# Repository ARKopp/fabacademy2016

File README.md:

#Fablab Academy 2016 - How to make anything

[BACK to START](start)

[FINAL PROJECT](final) / [WEEK 1](week1) / [COMPUTER AIDED DESIGN](week2) / [COMPUTER-CONTROLLED-CUTTING](week3) / [ELECTRONICS PRODUCTION](week4) / [3D SCANNING & PRINTING](week5) / [ELECTRONICS DESIGN 1](week6)  / [COMPUTER-CONTROLLED MACHINING](week7) / [EMBEDDED PROGRAMING ](week8) / [MECHANICAL AND MACHINE DESIGN](week9) / [INPUT DEVICES](week10) / [3D MOULDING AND CASTING ](week11) / [OUTPUT DEVICES](week12) /  [COMPOSITES](week13) / [EMBEDDED NETWORKING & COMMUNICATIONS](week14) / [INTERFACE AND APPLICATION PROGRAMMING ](week15) / [APPLICATIONS AND IMPLICATIONS ](week16) / [INVENTION, INTELLECTUAL PROPERTY, AND BUSINESS MODELS](week17) / [PROJECT DEVELOPMENT ](week18) /  

This year (2016) I will participate in the Fabacademy course called "How to make anything" with about 350 other students in over 80 Fablabs all over the world. I will participate at the Fablab Barcelona. On this website I will document my course acitivty and my [final project](final). The student websites of the bast years you find [here](http://archive.fabacademy.org/).

# About

Hi, I am Andreas a 32 year old guy from Munich Germany who makes a living tinkering and teaching kids coding and eletronics. Also I am building up my own fablab and raspberry pi academy at the moment focused on small and big kids called [erfindergarden](http://www.erfindergarden.de) and plan a fablab world tour after the academy program with my [Mincraft Hacking workshop](https://raspi-grundlagen-wien.eventbrite.de).

## My Story

I studied business and engineering and first started working in software sales. But I realized that beeing an employee is nothing for me so started working for myself in 2011.

My creazy journey started when I filmened and help creating a post-it art work of Steve Jobs at the Apple store after his death. This youtube video went viral and since then I have been creating [post-it art portraits](http://www.postitartreators.com) and pictures for conferences, commercials and art shows. 

In 2013 I build the [pixomat](http://www.pixomat.co) a pixel photobooth in a shopwindow on the other site of the street of the Steve Jobs portrait and since then got deeper and deeper into the maker world learning coding, electronics, raspberry pi, 3D Printing, Laser Cutting and since 2014 started teaching that knowledge to kids and also started freelancing for [hybris/SAP labs](http://labs.hybris.com) as a creative technologist.

## So why do I do the fabacademy ?

I want to gain deeper knowledge in the fablab technolgies and get to know other maker and share knowledge and experiences with them  I also think it is a good way to focus my energy on a project I have been dreaming to build for a while - [the stickomat](final).

## License

After filling out [these questions](https://creativecommons.org/choose/) on the creative commons website I decided to license this website and my work for fabacademy under a Creative Commons Attribution 4.0 International License.

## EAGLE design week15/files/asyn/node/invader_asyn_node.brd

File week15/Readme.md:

[BACK to START](../)

[FINAL PROJECT](../final) / [WEEK 1](../week1) / [COMPUTER AIDED DESIGN](../week2) / [COMPUTER-CONTROLLED-CUTTING](../week3) / [ELECTRONICS PRODUCTION](../week4) / [3D SCANNING & PRINTING](../week5) / [ELECTRONICS DESIGN](../week6)  / [COMPUTER-CONTROLLED MACHINING](../week7) / [EMBEDDED PROGRAMING ](../week8) / [MECHANICAL DESIGN](../week9) / [MACHINE DESIGN](../week10) / [INPUT DEVICES](../week11) / [3D MOULDING AND CASTING](../week12) / [OUTPUT DEVICES](../week13) / [COMPOSITES](../week14) / [EMBEDDED NETWORKING & COMMUNICATIONS](../week15) / [INTERFACE AND APPLICATION PROGRAMMING ](../week16) / [APPLICATIONS AND IMPLICATIONS ](../week17) / [INVENTION, INTELLECTUAL PROPERTY, AND BUSINESS MODELS](../week18) / [PROJECT DEVELOPMENT ](../week19)  

# Week 15 - Networking & Communications (WIP)

May 11 - May 18

[Lecture](http://academy.cba.mit.edu/classes/networking_communications/index.html), [Video](http://archive.fabacademy.org/archives/2016/master/videos/05-11/index.html)

~~~
*Weeks Assignment*

design and build a wired &/or wireless 
network connecting at least two processors

~~~

I can decided to make all the boards and started with the two Serial Boards. One is the node and one the bridge. 

## Invader Serial asynchronous

### Making Cabels 

First I put together 3 serial cables like for the FabISP as well. Then i started designing. 

### Node

* [x] Attiny 45
* [x] 2x3 Connector
* [x] 2x2 Connector
* [x] 1k Resistor
* [x] LED
* [x] 10K Resistor
* [x] 1uF Cap

This time no new components to look at. I just repositioned the LEDs to get an Invader eye. 

### Bridge

* [x] Attiny 45
* [x] 2x3 Connector
* [x] 2x2 Connector
* [x] 1K Resistor
* [x] LED
* [x] 10K Resistor
* [x] 1uF Cap
* [x] FTDI Connector

Because I wanted to position the FTDI connectors on the feet of the invader I had do add 6 0 Ohm. If you can figure out how to avoid that let me know. You can find the schematic and the brd file in the project files download link below.

### Milling and Stuffing 

Here my boards are in my other mill. I really got better in working with my mill after making all output devices. As I broke a bit because after pulling out one Invader the PCB was not sticking to the plate so good anymore I first finish milling all 4 invaders and the pull out all 4 at the same time or will use a smaller board when I only want to mill one little thing. 

## Programming 

The node I could program without problem. What you have to do is to assign the   bridge a 0 and the nodes a 1, 2, 2 etc.

## Invader Serial I2C

During the last years I worked with Arduino and Pis I always heared these three letters but never quite understood. 

So this time I first read a couple of articles about I-squared-C to understand it better. It was invented in 1982 to use as communication betweend Integrated Curcuits in CD Players and TVs. In Atmel I2X is called TWI (Two-Wire-Interface in their chops which is technically the same.

I2C needs two data lines. One seriell Clock line (SCL) and one for Data (SDA) and is used for communication for short distances. The speed is 100kbit/s standard and 10kbit/s low-speed mode. 

### Node

* [x] Attiny 45
* [x] 2x3 Connector
* [x] 2x2 Connector
* [x] 1k Resistor
* [x] LED
* [x] 3 x 10K Resistor
* [x] 1uF Cap

### Bridge

* [x] Attiny 45
* [x] 2x3 Connector
* [x] 2x2 Connector
* [x] 3x  10K Resistor
* [x] 1uF Cap
* [x] FTDI Connector

### Programming

When programming the node and the bridge with the c code you your are using the same code only that the bridge gets a `0` and the node gets a `1` you can then add more node with '2', '3' etc. 

###SPI (Serial Peripheral Interface)

Also when working with Arduino and Pi hats I have came across theses three letters SPI. Here a great [introduction](https://www.arduino.cc/en/Reference/SPI) of SPI on the Arduino homepage. 

For example I have the explorer hat from Pimorino. There the Raspberry pi would be the master and the the chip on the explorer hat would be the slave.

These are the lines used:

* MISO (Master In Slave Out) - The Slave line for sending data to the master,
* MOSI (Master Out Slave In) - The Master line for sending data to the peripherals,
* SCK (Serial Clock) - The clock pulses which synchronize data transmission generated by the master

and one line specific for every device:
* SS (Slave Select) - the pin on each device that the master can use to enable and disable specific devices.

### Invader Bluetooth

Coming up.

### Invader ESP

Coming up. 

## Project Files

[Download](https://drive.google.com/folderview?id=0B3iYmii-HJ7TOWdGSWFwd1ZlZG8&usp=sharing) all project files from this assignment from my Google Drive.

## Learnings

* get faster in designing in Eagle
* master my Othermill machine

## Feedback

[Twitter](http://www.twitter.com/andreaskopp) me or email me at [andreasrkopp at gmail dot com](mailto:andreasrkopp@gmail.com).

Or chat with me on gitter.

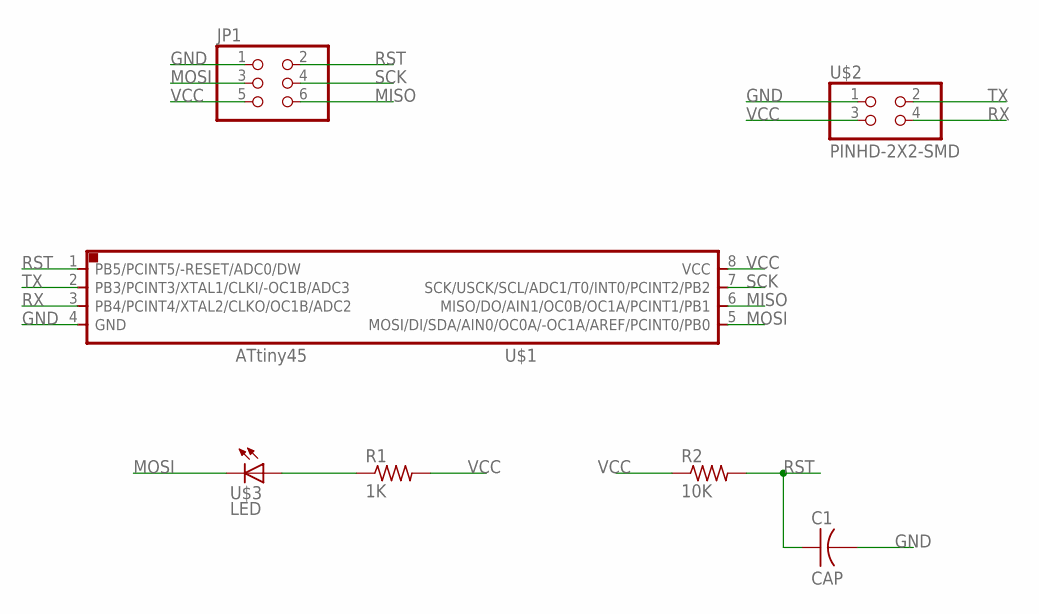
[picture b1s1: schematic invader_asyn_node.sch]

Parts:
C1: CAP; C1206FAB
JP1: PINHD-2X3-SMD; 2X03SMD
R1: 1K; R1206
R2: 10K; R1206
U$1: ATTINY45SI; SOIC8
U$2: PINHD-2X2-SMD; 2X02SMD
U$3: LED; LED1206FAB

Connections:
GND: C1.2, JP1.1, U$1.4 (GND), U$2.1
MISO: JP1.6, U$1.6 (MISO/DO/AIN1/OC0B/OC1A/PCINT1/PB1)
MOSI: JP1.3, U$1.5 (MOSI/DI/SDA/AIN0/OC0A/-OC1A/AREF/PCINT0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), U$3.2 (C)
unnamed: R1.1, U$3.1 (A)
RST: C1.1, JP1.2, R2.2, U$1.1 (PB5/PCINT5/-RESET/ADC0/DW)
RX: U$1.3 (PB4/PCINT4/XTAL2/CLKO/OC1B/ADC2), U$2.4
SCK: JP1.4, U$1.7 (SCK/USCK/SCL/ADC1/T0/INT0/PCINT2/PB2)
TX: U$1.2 (PB3/PCINT3/XTAL1/CLKI/-OC1B/ADC3), U$2.2
VCC: JP1.5, R1.2, R2.1, U$1.8 (VCC), U$2.3

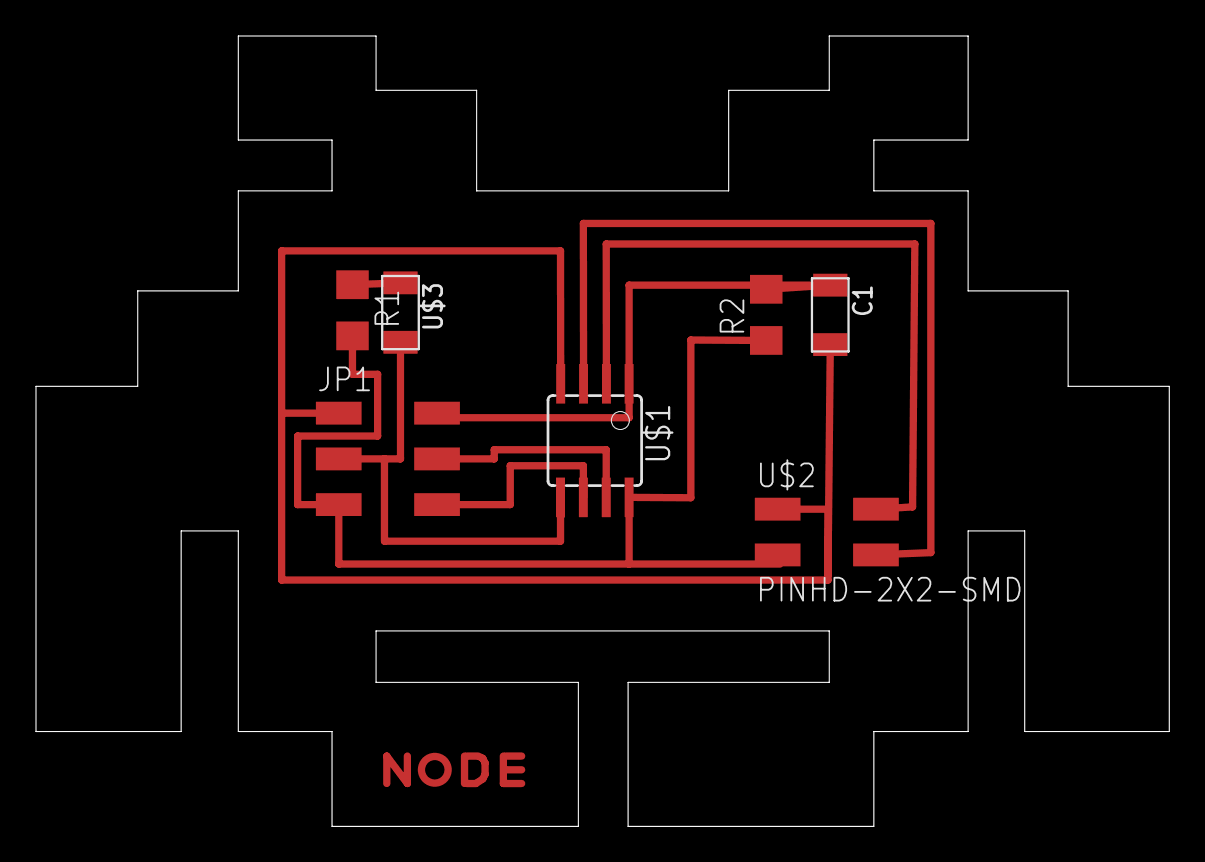
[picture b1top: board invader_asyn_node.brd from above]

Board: 2 copper layers, 63.0 x 43.9 mm, 7 parts (0 on the bottom side), 9 nets.

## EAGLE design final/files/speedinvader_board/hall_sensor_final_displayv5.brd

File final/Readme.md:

[BACK to START](../)

[FINAL PROJECT](../final) / [WEEK 1](../week1) / [COMPUTER AIDED DESIGN](../week2) / [COMPUTER-CONTROLLED-CUTTING](../week3) / [ELECTRONICS PRODUCTION](../week4) / [3D SCANNING & PRINTING](../week5) / [ELECTRONICS DESIGN](../week6)  / [COMPUTER-CONTROLLED MACHINING](../week7) / [EMBEDDED PROGRAMMING ](../week8) / [MECHANICAL DESIGN](../week9) / [MACHINE DESIGN](../week10) / [INPUT DEVICES](../week11) / [3D MOLDING AND CASTING](../week12) / [OUTPUT DEVICES](../week13) /  [COMPOSITES](../week14) / [EMBEDDED NETWORKING & COMMUNICATIONS](../week15) / [INTERFACE AND APPLICATION PROGRAMMING ](../week16) / [APPLICATIONS AND IMPLICATIONS ](../week17) / [INVENTION, INTELLECTUAL PROPERTY, AND BUSINESS MODELS](../week18) / [PROJECT DEVELOPMENT ](../week19)  

--------------------------------------------------------------------

***[Initial Idea  - the stickomat](./ideas)***

***[The Speedinvader](./)***

***[Process - How did I make it?](./process)***   

--------------------------------------------------------------------

## What did I make?

I made a bamboo composite skateboard and a skateboard speedometer that measures the speed with a magnetic sensor on the wheel of the board and displays it on a tiny oled display on top. 

But I learned to so much more in the last 6 months and most importantly I won friends from all over the world. Thank you all for the great time, your help and your couches. Also special thanks to my instructors Ferdi and Santi for your support. I could not have made it with you!

The Barcelona Fabacademy Class of 2016

## Final project video and Presentation

* [my final project Video live from the Chino infront of the Fablab Barcelona](../presentation.mp4)
* [presenting it to Neil Gerschenfield ](http://archive.fabacademy.org/archives/2016/master/videos/06-22/index.html)

## Composite Skateboard in week 14

I made the bamboo composite skateboard in [week14](../week14). 

## Bill of Materials (Version 7. Juli 2016)

* bamboo sheets 4 mm
* penny board wheels and beerings
* penny board axle
* black filament 
* one blank circuit board
* hall sensor
* tiny oled display
* Attiny85
* 4x 10k Resistor
* 1uF Capacitor
* 2 X SMD LEDs
* Battery Holder
* little neodyne magnet
* 2 Screws 

* [adafruit voltage booster](https://www.adafruit.com/products/2465)
* Lipo Battery 3,7 V

### What are my future plans for the project?

This is just a first version of the speedinvader. I could not complete all things I wanted to do but I want to keep on working.

* <del>Design and mill Hall Breakout v1</del>
* <del>Program Board v1<del>
* <del>Code for OLED Display in Arduino</del>
* <del>Add voice and Button v3</del>
* <del>Mill and solder board v3</del>
* <del>Design and mill Hall Breakout Double Sided</del>
* <del>Design Housing</del>
* <del>3D Print Housing</del>
* <del>make slide</del> 
* <del>make video</del>
* make a smaller board version
* make the breakoutboard fit better
* Design Waterproof Housing
* Mold Housing
* send board to be made in China
* make a bike version
* develop a workshop
* experiment with hex images

* optional: Raspberry Pi Zero HAT
* optional: add Bluetooth and Radio
* optional: Make a Light blue bean hat

##  Continue while Repositry locked

While the repository is locked I will continue to work on the speedinvader on my own git hub [here](github [here](https://github.com/ARKopp/fabacademy2016). 

## All files you need to rebuild it

It is still not perfect, so when you want to replicate this you may wont to wait a bit until I have made the next version. 

### Electronics

[hall_sensor_final_displayv5.brd](./files/speedinvader_board/hall_sensor_final_displayv5.brd)

[hall_sensor_final_displayv5.sch](./files/speedinvader_board/hall_sensor_final_displayv5.sch)

[hall_sensor_break_out.brd](./files/breakout_board/hall_sensor_break_out.brd)

[hall_sensor_break_out.sch](./files/breakout_board/hall_sensor_break_out.sch)

### Code

[firmwarespeedinvader.ino (you need all libraries)](./files/firmware_speedinvader/firmware_speedinvader)

### Skateboard

[skateboard design (rhino)](../week14/files/skateboard_file.3dm)

### Case

[CaseBottom, Case Top, Skateboard Holder (Tinkercad)](https://tinkercad.com/things/1azkU2S8nCk)

[CaseTop](./files/design_files/case_top.stl)

[CaseBottom](./files/design_files/scase_bottom.stl)

[Skateboard Mount](./files/design_files/skateboard_mount.stl)

I will make speedinvader PCB much smaller because I do not think that is very practical.

## Feedback ?

[Twitter](http://www.twitter.com/andreaskopp) me or [email me at andreasrkopp at gmail dot com](mailto:andreasrkopp@gmail.com) I am very happy to help. 

Or chat with me on gitter.

## License

In [week18 ](../week18) I chose the license for the speedinvader. 

The project is licensed under Attribution-ShareAlike 4.0 International (CC BY-SA 4.0). So if you are creating a derivative of my speedometer you should license it as well under CC BY-SA 4.0 license and credit me like above. This is the same license Arduino is using for their hardware.

[BACK to TOP](../final)

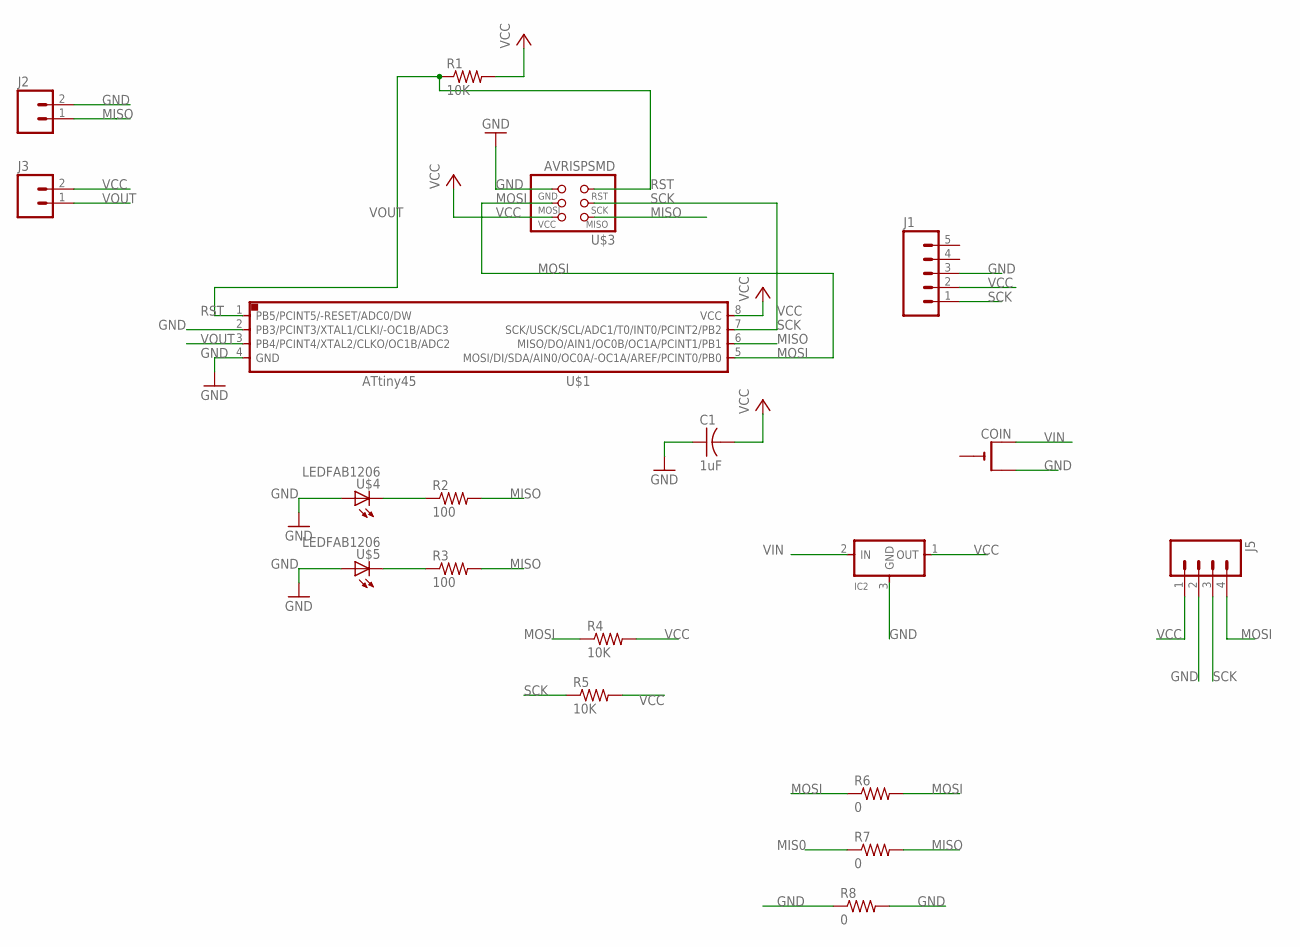
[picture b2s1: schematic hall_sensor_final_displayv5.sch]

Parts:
C1: 1uF; C1206FAB
COIN: CR2032THM; CR2032-THRU
IC2: REGULATORSOT23; SOT23
J1: M05LOCK; 1X05_LOCK
J2, J3: M02POLAR_LOCK; MOLEX-1X2_LOCK
J5: M04LOCK; 1X04_LOCK
R1, R4, R5: 10K; R1206FAB
R2, R3: 100; R1206FAB
R6, R7, R8: 0; R1206FAB
U$1: ATTINY45SI; SOIC8
U$3: AVRISPSMD; 2X03SMD
U$4, U$5: LEDFAB1206; LED1206FAB

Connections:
GND: C1.1, COIN.+2 (+1), IC2.3 (GND), J1.3, J2.2, J5.2, R8.1, R8.2, U$1.2 (PB3/PCINT3/XTAL1/CLKI/-OC1B/ADC3), U$1.4 (GND), U$3.6 (GND), U$4.1 (A), U$5.1 (A)
MIS0: R7.1
MISO: J2.1, R2.2, R3.2, R7.2, U$1.6 (MISO/DO/AIN1/OC0B/OC1A/PCINT1/PB1), U$3.1 (MISO)
MOSI: J5.4, R4.1, R6.1, R6.2, U$1.5 (MOSI/DI/SDA/AIN0/OC0A/-OC1A/AREF/PCINT0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), U$3.4 (MOSI)
unnamed: R2.1, U$4.2 (C)
unnamed: R3.1, U$5.2 (C)
RST: R1.1, U$1.1 (PB5/PCINT5/-RESET/ADC0/DW), U$3.5 (RST)
SCK: J1.1, J5.3, R5.1, U$1.7 (SCK/USCK/SCL/ADC1/T0/INT0/PCINT2/PB2), U$3.3 (SCK)
VCC: C1.2, IC2.1 (OUT), J1.2, J3.2, J5.1, R1.2, R4.2, R5.2, U$1.8 (VCC), U$3.2 (VCC)
VIN: COIN.+1 (+), IC2.2 (IN)
VOUT: J3.1, U$1.3 (PB4/PCINT4/XTAL2/CLKO/OC1B/ADC2)

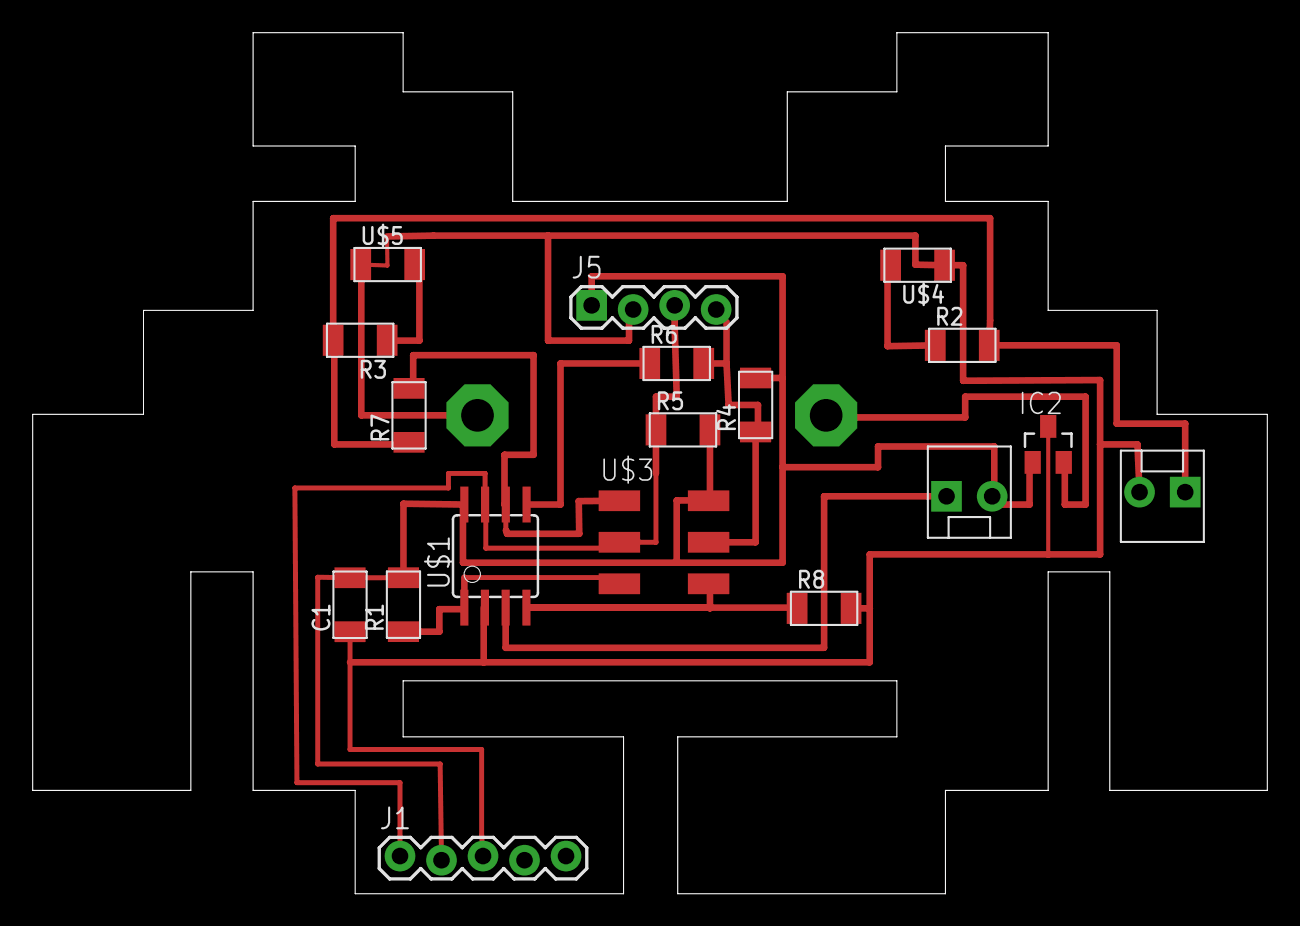
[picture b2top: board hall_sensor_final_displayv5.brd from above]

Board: 2 copper layers, 75.6 x 52.7 mm, 19 parts (1 on the bottom side), 10 nets.

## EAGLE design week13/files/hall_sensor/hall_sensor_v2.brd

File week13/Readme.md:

[BACK to START](../)

[FINAL PROJECT](../final) / [WEEK 1](../week1) / [COMPUTER AIDED DESIGN](../week2) / [COMPUTER-CONTROLLED-CUTTING](../week3) / [ELECTRONICS PRODUCTION](../week4) / [3D SCANNING & PRINTING](../week5) / [ELECTRONICS DESIGN](../week6)  / [COMPUTER-CONTROLLED MACHINING](../week7) / [EMBEDDED PROGRAMING ](../week8) / [MECHANICAL DESIGN](../week9) / [MACHINE DESIGN](../week10) / [INPUT DEVICES](../week11) / [3D MOLDING AND CASTING](../week12) / [OUTPUT DEVICES](../week13) / [COMPOSITES](../week14) / [EMBEDDED NETWORKING & COMMUNICATIONS](../week15) / [INTERFACE AND APPLICATION PROGRAMMING ](../week16) / [APPLICATIONS AND IMPLICATIONS ](../week17) / [INVENTION, INTELLECTUAL PROPERTY, AND BUSINESS MODELS](../week18) / [PROJECT DEVELOPMENT ](../week19)

# Week 13 - OUTPUT DEVICES

May 10

[Lecture](http://academy.cba.mit.edu/classes/output_devices/index.html), [Video](http://archive.fabacademy.org/archives/2016/master/videos/04-20/index.html)

~~~
*Weeks Assignment*

* add an output device to a micro controller board you've designed 
* program it to do something

~~~

For this assignment I decided to get the LEDs of my space invader to work and make a second version with two RGB LEDs. In the end I did all output devices and made a little invader army.

## Change the code to turn on the LEDs

For [Input Devices](../week11) I had made a space invader but failed to get the LEDs to turn on. 

I first checked if I had soldered them correctly with the Green Line to the Ground. And I had. I also checked the Resistor Value again. I used the red LED and after looking into the [Fabacademy Inventory](https://docs.google.com/spreadsheets/d/1U-jcBWOJEjBT5A0N84IUubtcHKMEMtndQPLCkZCkVsU/pub?single=true&gid=0&output=html) I found the Red Led had the number 160-1167-2-ND. Looking that up on the digikey website I found the Forward Voltage is 1.8 V and the forwward current is 40 mA which result in a Resistor of 82 Ohms and I am using 499 Ohms at the moment so I will change the resistor to 100 Ohms. 

***Update 8. Mai 2016:***

I changed the Resistors from 499 Ohm to 100 Ohms and finally got the invader eyes to light up! But the LEDs I connected to and MOSI and MISO which turned out to be Pin 0 and Pin 1 in then Arduino IDE.

***Update 14. Mai 2016:***

Next I wanted to get finally get my hall effect Sensor working. The sensor has 3 legs, VCC, GND and VOUT which I connected to PB4. 

Because I still did not learn enough C I looked for some Arduino Code. 

But I found [some code](http://playground.arduino.cc/Code/HallEffect) on the Arduino Website and some other code [here](http://www.hobbytronics.co.uk/arduino-tutorial11-hall-effect) and [here](http://www.instructables.com/id/DIY-bike-tachometer/step3/Upload-code/).

Still I was not able to get any reading. 

I check with the python file from Neil and with a different cable but still no reading. So I think I destroyed my sensor somehow. I will check the sensor on an Arduino to see if its really the sensor. 

***Update 22. Mai 2016:***

I finally found the time to revise my space invader board and added a through hole connector, I think the chance that they break off is much lower then the ISP Connectors that only have a connection with the top of the board. You can find the design in the project download in input devices. I think I found this connector in the sparkfun library (Eagle: 1x5 Lock).

http://www.instructables.com/id/Hall-effect-sensor/step2/Range-of-a-Hall-effect-Sensor/

http://www.instructables.com/id/Arduino-Skateboard-Speedometer/step3/The-Arduino-Code/

http://www.instructables.com/id/DIY-SPEEDOMETER-AND-ODOMETER/step3/THE-CODE/

## Invader RGB

Next I wanted to turn my invader into an RGB Invader. Also I wanted to avoid doing the fabmodules step and the step to turn create the black and white images. I first Vectorized my space invader image with Inkscape and exported as dxf and imported into Eagle in the Dimension Layer with File>Import>DXF.

I started with Neils Design and added another LED and resistor.  

### Bill of Material

* [x] 1 x RGB Led
* [x] 2 x 1k Resistor 
* [x] 1 x 499 ohm
* [x] 1x 1Ok Resistor
* [x] 1 x 1uF Capacitor
* [x] 1x Attiny 45
* [x] 1x 2X3 AVR ISP Connector
* [x] 1x 2X2 AVR ISP Connector (Eagle:PINHD-2x2-SMD) <--- look exactly with this name when your searching
* [x] 1x LM3480IM3-5.0 Voltage Regulator (Eagle: RegulatorSot23)
* [x] 1x 100 Ohm Resistor
* [x] 1x Red LED

### Schematic and Board Design

First I looked at the Datasheet of the RGB LED to find how I need to connect it. 

I connected it like this. 

Then I added all the parts to the board. I had some problems to find the Voltage Regulator and the 2x2 Connector but managed in the end. 

It was the first time I used the 5V Voltage Regulator 100MA (LM3480IM3-5.0/NOPBCT-ND) so I looked it on Digikey and found out the you can put in as much as 30V and it always puts out 5V.

***Update 17. Mai 2016***

After doing all the output board I realized that their are two different 5V voltage regulators in the Inventory one small one with a small 100mA footprint (LM3480IM3-3.3/NOPBCT-ND)  ... 

and a 1A one (LM3480IM3-5.0/NOPBCT-ND) with a big foot print. 

All the boards are usign the small one only the SERVO board is using the big one. 

For my RGB Board with the extra LED I did not manange to connect the RGB and the LED with out adding a O Ohm Resistor and two jumpers. 

In the end I did a new board just with one RGB LED. 

```
sudo make -f hello.speaker.45.make program-avrisp2

```

### Milling

I saved the Brd file and milled with my Othermill.  

### Stuffing and Programming 

Then I stuffed the board and tried to program it but got an error. Only after checking all connections and using another ISP I found that I had positioned the RGB LED wrongly. The little white corner is not the Power put R for Red. In my case it is on the right top side. 

For Programming you download the [Make](http://academy.cba.mit.edu/classes/output_devices/LCD/hello.LCD.44.make) and the [C](http://academy.cba.mit.edu/classes/output_devices/LCD/hello.LCD.44.c) file into a folder and open them in Terminal. Because I stepped on my FabISP and damaged the connector I used the AVRisp I bought. I also find it quite difficult to remember the GND and VCC Side of the Cable of my FabISP.  

I would love to do some screen printing soon to print lables on the boards before I mill them. 

```
sudo make -f hello.RGB.45.make program-avrisp2

```
And it was successful! Because I could not get my board to work but the second board without the extra LED worked.

The first board I also tried to fix but damaged the Pads of the LED when desoldering and could not fix it again.

### Invader LCD Screen

* [x] Attiny44
* [x] 20 MHz Resonator
* [x] 10 K Resistor
* [x] 2x3 ISP Connector
* [x] 1 uF Cap
* [x] 5V Voltage Regulator
* [x] 100 K Resistor
* [x] 1K Resistor
* [x] 5x2 Connector
* [x] 2x3 Connector

### Invader Speaker

* [x] speaker
* [x] Attiny45
* [x] 10k Resistor
* [x] Voltage Regulator 5V
* [x] 2X 2x2 Connector
* [x] 1X 2x3 Connector

Only after I did not get a green light with my AVR I realized that I forgot a connection in my schematic bitween the VCC and the 10K Resistor. After fixing that with a little wire I finally got the greenlight and programmed it. 

```
sudo make -f hello.speaker.45.make program-avrisp2
```

Thank you!

### Invader Servo

* [x] Attiny44
* [x] 10 K Resistor
* [x] 20 Mhz Resonator
* [x] 22 uF Capacitor
* [x] 5 V Voltage Regulator Big 1A (Eagle: 
* [x] 2x 3x2 ISP Connectors
* [x] 2x2 ISP Connectors
* [x] 0 Ohm 

### Invader Brush DC

To control the DC Motor we need a [H-Bridge](http://www.digikey.com/product-detail/en/A4953ELJTR-T/620-1428-1-ND/2765622). A DC Motor can only run at one speed and  forward or backwards. So I am using a A4952 from Allegro to turn the Motor on and off really fast to control the speed this way. 

* [x] Attiny44
* [x] 10K Resistor
* [x] 10uF Cap
* [x] 2x 1uF Cap
* [x] A 4953 H-Bridge
* [x] 5 V Voltage Regulator
* [x] 2x  2x2 ISP Conncetors

First I forget to connect some line but I realized it before soldering. Here I realize I have to be more careful and check all lines and if I have added all components. So I milled again and finished the board. 

Always I have to cut the line for the voltage generator with a knife. So I wander how can I avoid this?

### Invader Stepper Uni

* [x] Attiny44
* [x] 3 x 1uF Capacitator 
* [x] 2 x 10uF Capacitator (I forgot this at first!)
* [x] 10 K
* [x] 5 V Regulator
* [x] 2 X 2x3 Connectors
* [x] 2x2 Connector
* [x] 4 x N Mosef

### Invader LED Array (coming soon)

This one I would like to do on a two sided PCB. So I have the microcontroller on the back and all the led on the front of the Invader. 

* 20 X O hm 
* 5 x 499 Ohm
* 1 uF
* 10 K Resistor
* 2x3 ISP Connector
* 2x2 ISP Connector
* Voltage Regulator 5V

### Invader Video (Coming soon)

Coming soon. 

* [x] Attiny44
* [x] 20 MHz Resonator
* [x] 10 K Resistor
* [x] 1 K Resistor
* [x] 1 uF Cap
* [x] 499 Resistor
* [x] 2x2 Connector
* [x] 5x2 Connector

## Project Files

[Download](https://drive.google.com/folderview?id=0B3iYmii-HJ7TdHh1VUJGRzdHalE&usp=sharing) all project files I ued for this assignment from my Google Drive. I have uploaded the improved invader_hall and the invader_rgb also to the repository. Also I made an invader with a coin cell battery that I linked here. 

[invader-rgb_working.brd](.files/invader_rgb/invader-rgb_working.brd)

[invader-rgb_working.sch (save as)](.files/invader_rgb/invader-rgb_working.sch)

[hall_sensor_v2.sch](.files/hall_sensor/hall_sensor_v2.sch)

[invader_vector_final.dxf (file I imported on Dimension 20 Layer)](./files/invader_vector_final.dxf)

[invader_coin2.brd](.files/invader_coin/invader_coin2.brd)   

[invader_coin2.sch (save as) ](.files/invader_coin/invader_coin2.sch)

## Learnings

* get faster in designing in Eagle
* master my Othermill machine
* understand all electronic components used better
* trouble shoot a board (first check all connections from connector to chip, shorts on connector, then if chip gets 5V)

## Feedback

[Twitter](http://www.twitter.com/andreaskopp) me or [email me at andreasrkopp at gmail dot com](mailto:andreasrkopp@gmail.com).

Or chat with me on gitter.

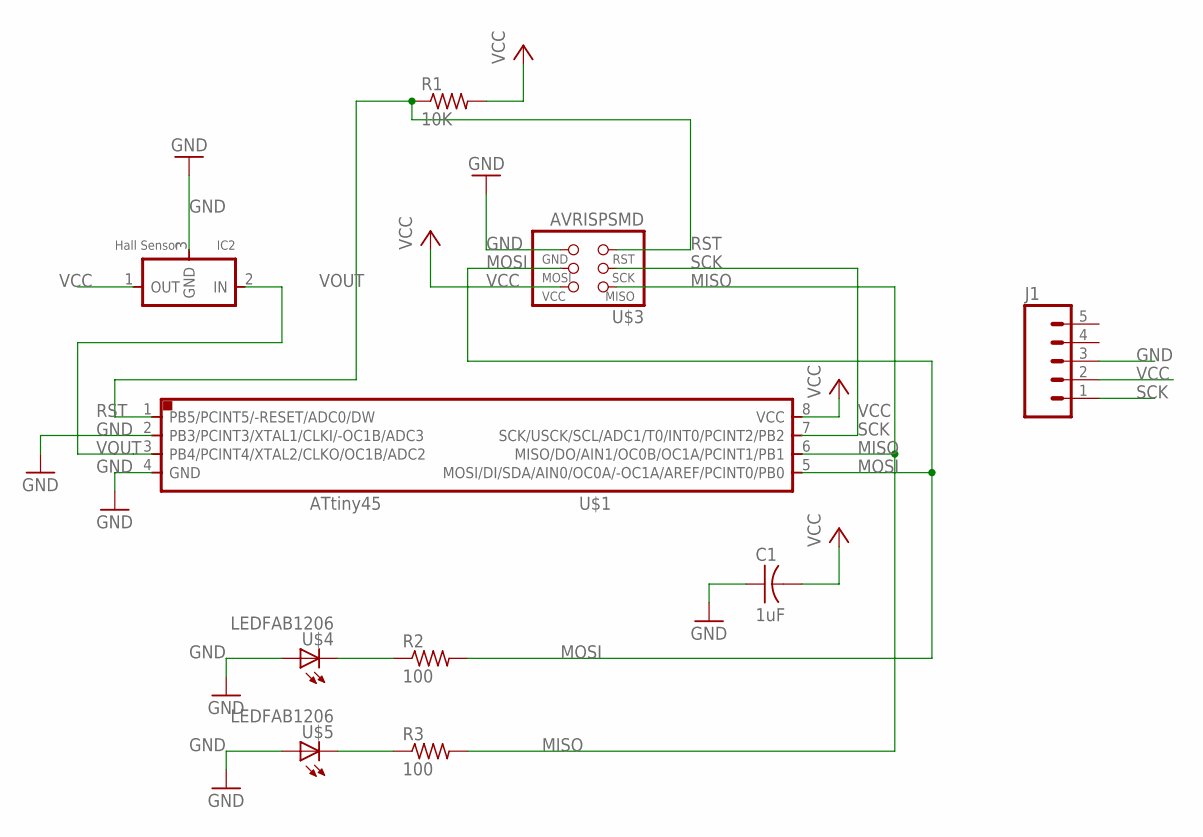
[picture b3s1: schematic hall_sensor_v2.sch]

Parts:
C1: 1uF; C1206FAB
IC2: Hall Sensor; SOT23
J1: M05LOCK; 1X05_LOCK
R1: 10K; R1206FAB
R2, R3: 100; R1206FAB
U$1: ATTINY45SI; SOIC8
U$3: AVRISPSMD; 2X03SMD
U$4, U$5: LEDFAB1206; LED1206FAB

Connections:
GND: C1.1, IC2.3 (GND), J1.3, U$1.2 (PB3/PCINT3/XTAL1/CLKI/-OC1B/ADC3), U$1.4 (GND), U$3.6 (GND), U$4.1 (A), U$5.1 (A)
MISO: R3.2, U$1.6 (MISO/DO/AIN1/OC0B/OC1A/PCINT1/PB1), U$3.1 (MISO)
MOSI: R2.2, U$1.5 (MOSI/DI/SDA/AIN0/OC0A/-OC1A/AREF/PCINT0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), U$3.4 (MOSI)
unnamed: R2.1, U$4.2 (C)
unnamed: R3.1, U$5.2 (C)
RST: R1.1, U$1.1 (PB5/PCINT5/-RESET/ADC0/DW), U$3.5 (RST)
SCK: J1.1, U$1.7 (SCK/USCK/SCL/ADC1/T0/INT0/PCINT2/PB2), U$3.3 (SCK)
VCC: C1.2, IC2.1 (OUT), J1.2, R1.2, U$1.8 (VCC), U$3.2 (VCC)
VOUT: IC2.2 (IN), U$1.3 (PB4/PCINT4/XTAL2/CLKO/OC1B/ADC2)

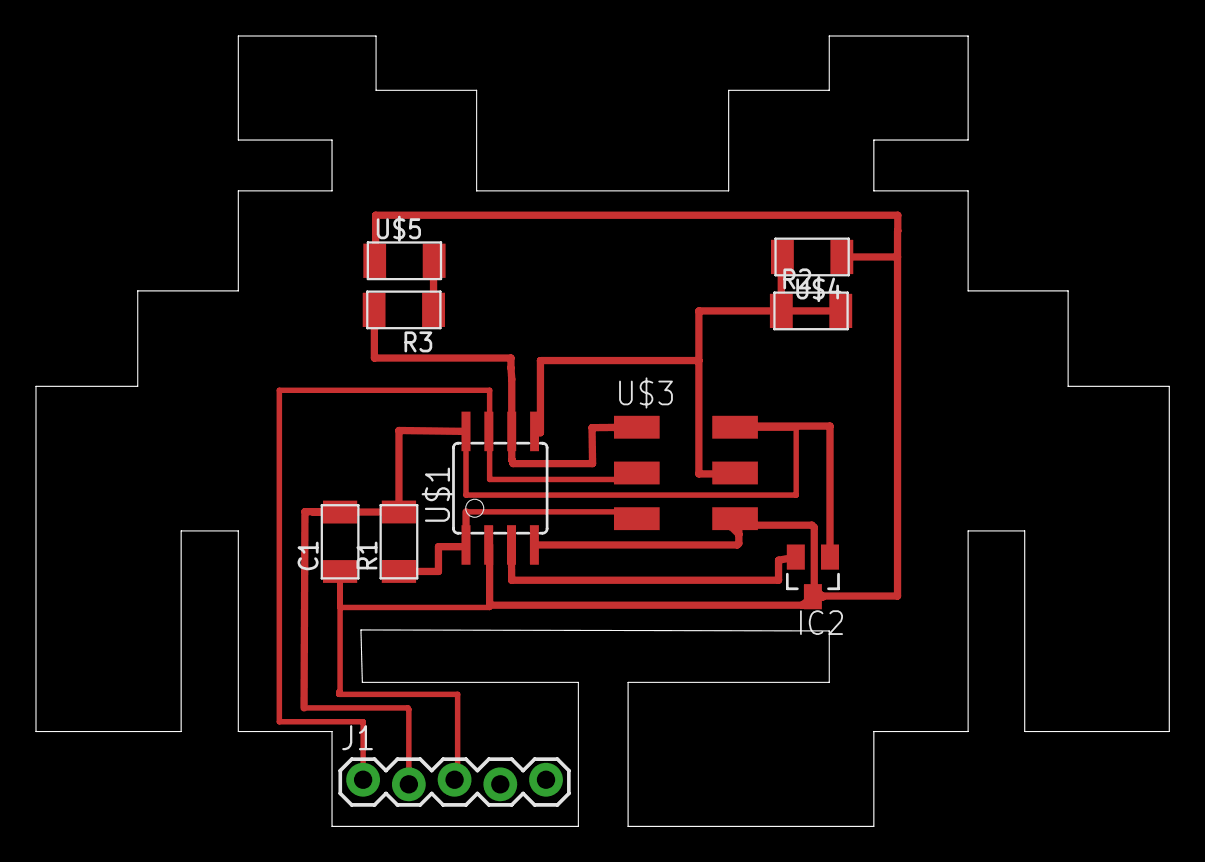
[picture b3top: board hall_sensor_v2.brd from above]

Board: 2 copper layers, 63.0 x 43.9 mm, 10 parts (0 on the bottom side), 9 nets.

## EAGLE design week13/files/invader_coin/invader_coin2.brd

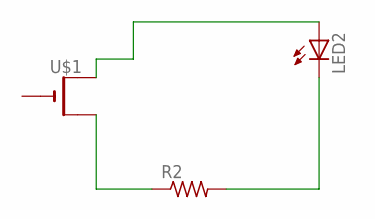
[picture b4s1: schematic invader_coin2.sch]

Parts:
LED2: LED5MM
R2: R-US_0309/12; 0309/12
U$1: CR2032THM; CR2032-THRU

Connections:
unnamed: LED2.A, U$1.+1 (+)
unnamed: R2.1, U$1.+2 (+1)
unnamed: LED2.K (C), R2.2

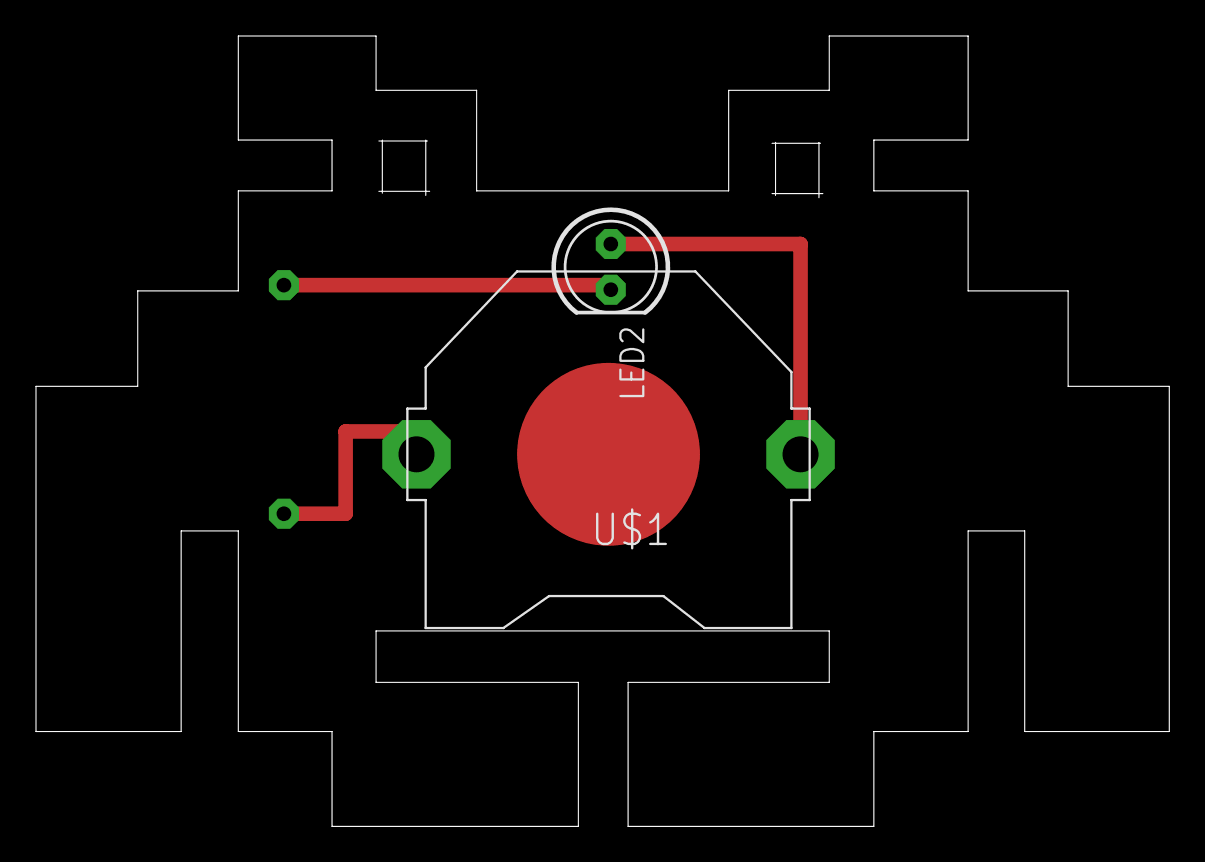
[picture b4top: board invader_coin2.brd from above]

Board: 2 copper layers, 63.0 x 43.9 mm, 3 parts (1 on the bottom side), 3 nets.

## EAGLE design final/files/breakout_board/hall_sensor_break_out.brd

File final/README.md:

[START HERE] (start) / [ABOUT ME](about) / [FINAL PROJECT] (final) / [WEEK 1](week1) / [COMPUTER AIDED DESIGN](week2) / [COMPUTER-CONTROLLED-CUTTING](week3) / [ELECTRONICS PRODUCTION](week4) / [3D SCANNING & PRINTING](week5) / [ELECTRONICS DESIGN 1](week6)  / [COMPUTER-CONTROLLED MACHINING](week7) / [EMBEDDED PROGRAMING ](week8) / [MECHANICAL AND MACHINE DESIGN](week9) / [INPUT DEVICES](week10) / [3D MOULDING AND CASTING ](week11) / [OUTPUT DEVICES](week12) /  [COMPOSITES](week13) / [EMBEDDED NETWORKING & COMMUNICATIONS](week14) / [INTERFACE AND APPLICATION PROGRAMMING ](week15) / [APPLICATIONS AND IMPLICATIONS ](week16) / [INVENTION, INTELLECTUAL PROPERTY, AND BUSINESS MODELS](week17) / [PROJECT DEVELOPMENT ](week18) /

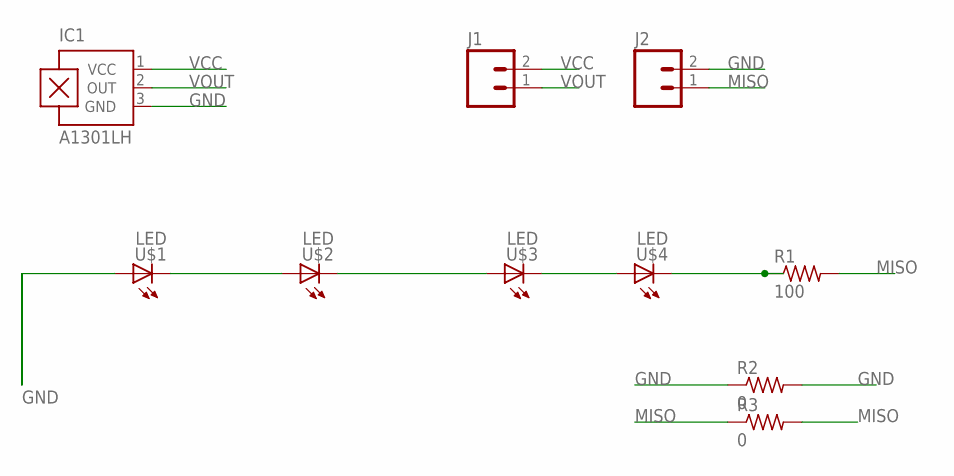
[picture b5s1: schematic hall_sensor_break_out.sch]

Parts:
IC1: A1301LH; SOT23-W
J1, J2: M02POLAR_LOCK; MOLEX-1X2_LOCK
R1: 100; R1206FAB
R2, R3: 0; R1206FAB
U$1, U$2, U$3, U$4: LED; LED1206

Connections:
GND: IC1.3 (GND), J2.2, R2.1, R2.2, U$1.1 (A)
MISO: J2.1, R1.2, R3.1, R3.2
unnamed: U$1.2 (C), U$2.1 (A)
unnamed: U$2.2 (C), U$3.1 (A)
unnamed: U$3.2 (C), U$4.1 (A)
unnamed: R1.1, U$4.2 (C)
VCC: IC1.1 (VCC), J1.2
VOUT: IC1.2 (OUT), J1.1

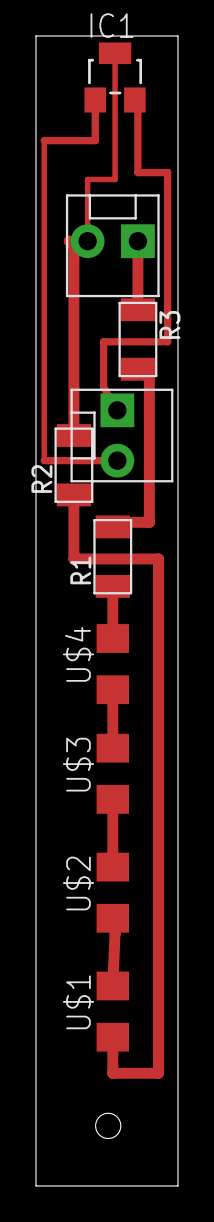
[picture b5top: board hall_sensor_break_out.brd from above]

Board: 2 copper layers, 7.9 x 63.9 mm, 10 parts (0 on the bottom side), 8 nets.

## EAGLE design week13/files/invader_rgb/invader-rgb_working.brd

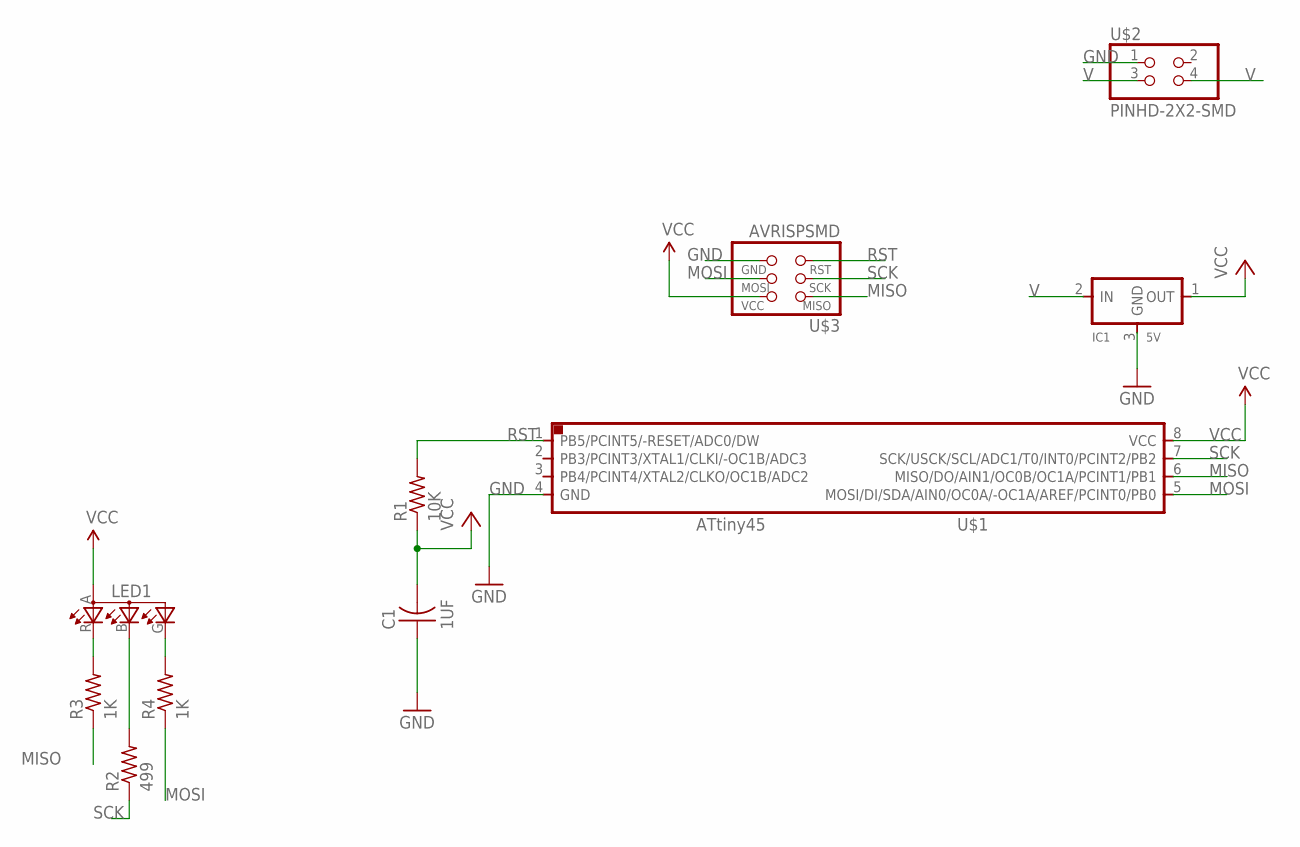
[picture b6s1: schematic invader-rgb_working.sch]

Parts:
C1: 1UF; C1206FAB
IC1: 5V; SOT23
LED1: LEDRGBOLD; P-LCC-4-3
R1: 10K; R1206FAB
R2: 499; R1206FAB
R3, R4: 1K; R1206FAB
U$1: ATTINY45SI; SOIC8
U$2: PINHD-2X2-SMD; 2X02SMD
U$3: AVRISPSMD; 2X03SMD

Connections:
GND: C1.1, IC1.3 (GND), U$1.4 (GND), U$2.1, U$3.6 (GND)
MISO: R3.1, U$1.6 (MISO/DO/AIN1/OC0B/OC1A/PCINT1/PB1), U$3.1 (MISO)
MOSI: R4.1, U$1.5 (MOSI/DI/SDA/AIN0/OC0A/-OC1A/AREF/PCINT0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), U$3.4 (MOSI)
unnamed: LED1.R (CRED), R3.2
unnamed: LED1.B (CBLUE), R2.2
unnamed: LED1.G (CGREEN), R4.2
RST: R1.2, U$1.1 (PB5/PCINT5/-RESET/ADC0/DW), U$3.5 (RST)
SCK: R2.1, U$1.7 (SCK/USCK/SCL/ADC1/T0/INT0/PCINT2/PB2), U$3.3 (SCK)
V: IC1.2 (IN), U$2.3, U$2.4
VCC: C1.2, IC1.1 (OUT), LED1.A (A2), R1.1, U$1.8 (VCC), U$3.2 (VCC)

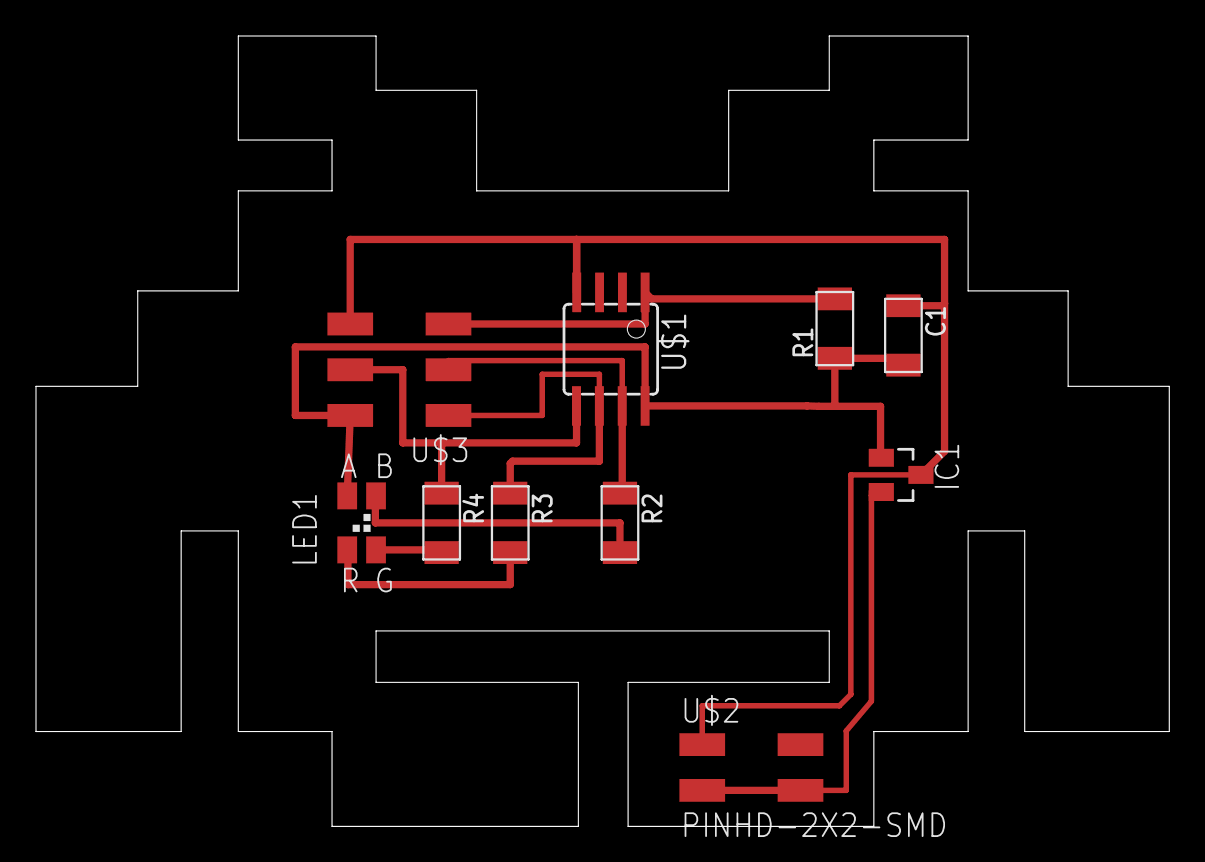
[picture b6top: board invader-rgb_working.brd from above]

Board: 2 copper layers, 63.0 x 43.9 mm, 10 parts (0 on the bottom side), 10 nets.

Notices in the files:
parts and their libraries:
SparkFun-Connectors: Licensing: Creative Commons ShareAlike 4.0 International - https://creativecommons.org/licenses/by-sa/4.0
